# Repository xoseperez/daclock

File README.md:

# DA CLOCK

This repository contains the schematics and board layouts for Eagle of the different DaClock versions I've done so far.
The common parts between all these versions are: a microcontroller on board with some power management, an RTC and connectors for LED strips or matrices.

Current version is 3.0, based on ESP8266 and DS1337S, also features a buzzer and support for both WS2812 strips/matrices and 5050 "single color" strips.

## Versions

### Version 3.0 - WIFI LITE

This is the latest version of the DA CLOCK board, a custom ESP8266-based clock with an RTC, a buzzer and output to handle WS2812 strips.

#### Bill of materials for a WS2812-based clock

|Item|Buy|Quantity|CPU <sup>units</sup>|Total|
|---|---|---|---|---|
|Tinkerman Da Clock WIFI 3.0|[OSH Park](https://oshpark.com/shared_projects/gDLQyM9I)|1|6.57€ <sup>3</sup>|6.57€|
|Ai-Thinker ESP12F|[Aliexpress](http://s.click.aliexpress.com/e/mUZjemI) / [Ebay](https://rover.ebay.com/rover/1/711-53200-19255-0/1?icep_id=114&ipn=icep&toolid=20004&campid=5338044841&mpre=http%3A%2F%2Fwww.ebay.com%2Fitm%2FESP8266-Remote-Serial-Port-WIFI-Transceiver-Wireless-Module-Esp-12F-AP-STA-%2F272408386985%3Fhash%3Ditem3f6cce1da9%3Ag%3ArywAAOSwZJBX-7RV)|1|2.10€ <sup>5</sup>|2.10€|
|AMS1117-3.3|[Aliexpress](http://s.click.aliexpress.com/e/uj6iuNv) / [Ebay](https://rover.ebay.com/rover/1/711-53200-19255-0/1?icep_id=114&ipn=icep&toolid=20004&campid=5338044841&mpre=http%3A%2F%2Fwww.ebay.com%2Fitm%2FNew-10pcs-AMS1117-LM1117-3-3V-1A-SOT-223-Voltage-Regulator-NT00206-Ship-Today-%2F112049991237%3Fhash%3Ditem1a16b32e45%3Ag%3AqV8AAOSw14xWNwXc)|1|0.03€ <sup>50</sup>|0.03€|
|DS1337S|[Aliexpress](http://s.click.aliexpress.com/e/qbaAUr3) / [Ebay](https://rover.ebay.com/rover/1/711-53200-19255-0/1?icep_id=114&ipn=icep&toolid=20004&campid=5338044841&mpre=http%3A%2F%2Fwww.ebay.com%2Fitm%2F10-PCS-DS1337S-SOP-8-DS1337-1337-SMD-I2C-Serial-Real-Time-Clock-New-Original-%2F291774646835)|1|0.62€ <sup>10</sup>|0.62€|
|32KHz crystal|[Aliexpress](http://s.click.aliexpress.com/e/UVrrFmU) / [Ebay](https://rover.ebay.com/rover/1/711-53200-19255-0/1?icep_id=114&ipn=icep&toolid=20004&campid=5338044841&mpre=http%3A%2F%2Fwww.ebay.com%2Fitm%2FRALTRON-32-768KHz-Crystal-R38-32-768KHZ-R38-Style-Qty-10-%2F161261371100)|1|0.03€ <sup>50</sup>|0.03€|
|1N4148 SMD Diode|[Aliexpress](http://s.click.aliexpress.com/e/i2nayrB)|1|0.14€ <sup>10</sup>|0.14€|
|Buzzer|[Aliexpress](http://s.click.aliexpress.com/e/VbeAu3z) / [Ebay](https://rover.ebay.com/rover/1/711-53200-19255-0/1?icep_id=114&ipn=icep&toolid=20004&campid=5338044841&mpre=http%3A%2F%2Fwww.ebay.com%2Fitm%2FNew-10pcs-5v-Active-Buzzer-Continous-Beep-High-quality-The-sound-Alarm-HT00202-%2F281280117872)|1|0.15€<sup>10</sup>|0.15€|
|S8550 SMD NPN transistor|[Aliexpress](http://s.click.aliexpress.com/e/VZ3FYN7)|2|0.02€<sup>100</sup>|0.04€|
|100nF 0805 ceramic capacitor||1|0.01€ <sup>100</sup>|0.01€|
|1uF 10V 0805 tantalum capacitor|[Aliexpress](http://s.click.aliexpress.com/e/ey3ZVn2)|2|0.06€ <sup>50</sup>|0.12€|
|1000uF 16V electrolytic SMD capacitor|[Aliexpress](http://s.click.aliexpress.com/e/MjQ7eMf)|1|0.19€ <sup>10</sup>|0.19€|
|200Ohm 0805 resistor||1|0.01€ <sup>100</sup>|0.01€|
|10KOhm 0805 resistor||7|0.01€ <sup>100</sup>|0.07€|
|2 positions 5mm screw terminal|[Aliexpress](http://s.click.aliexpress.com/e/a2fqnM7)|1|0.06€ <sup>100</sup>|0.06€|
|3 positions 5mm screw terminal|[Aliexpress](http://s.click.aliexpress.com/e/Vjaa2RB)|1|0.07€ <sup>100</sup>|0.07€|
|3 position male header||1|0.01€ <sup>100</sup>|0.01€|
|5 position male header||1|0.01€ <sup>100</sup>|0.01€|
|Jumper||1|0.01€ <sup>100</sup>|0.01€|
|**Total**||||10.25€|

* (units) Minimum quantity for the stated price.
* Prices are based on the cheapest option, usually Aliexpress.
* Check the schematic (image or eagle file) for relation between parts and values.

### Version 2.1 - WIFI

### Version 1.2

## Firmware

* Project [Wordclock](https://bitbucket.org/xoseperez/wordclock) uses version 1.0 of this board (atmega328p based).
- Project [Slices](http://github.com/xoseperez/slices) uses version 3.0 of this board (ESP8266 based).

## Open Hardware

Hardware designs (schematics and CAD) files are licensed under the [Creative Commons Attribution-ShareAlike 3.0 Unported License](http://creativecommons.org/licenses/by-sa/3.0/) and follow the terms of the [OSHW (Open-source hardware) Statement of Principles 1.0.](http://freedomdefined.org/OSHW)

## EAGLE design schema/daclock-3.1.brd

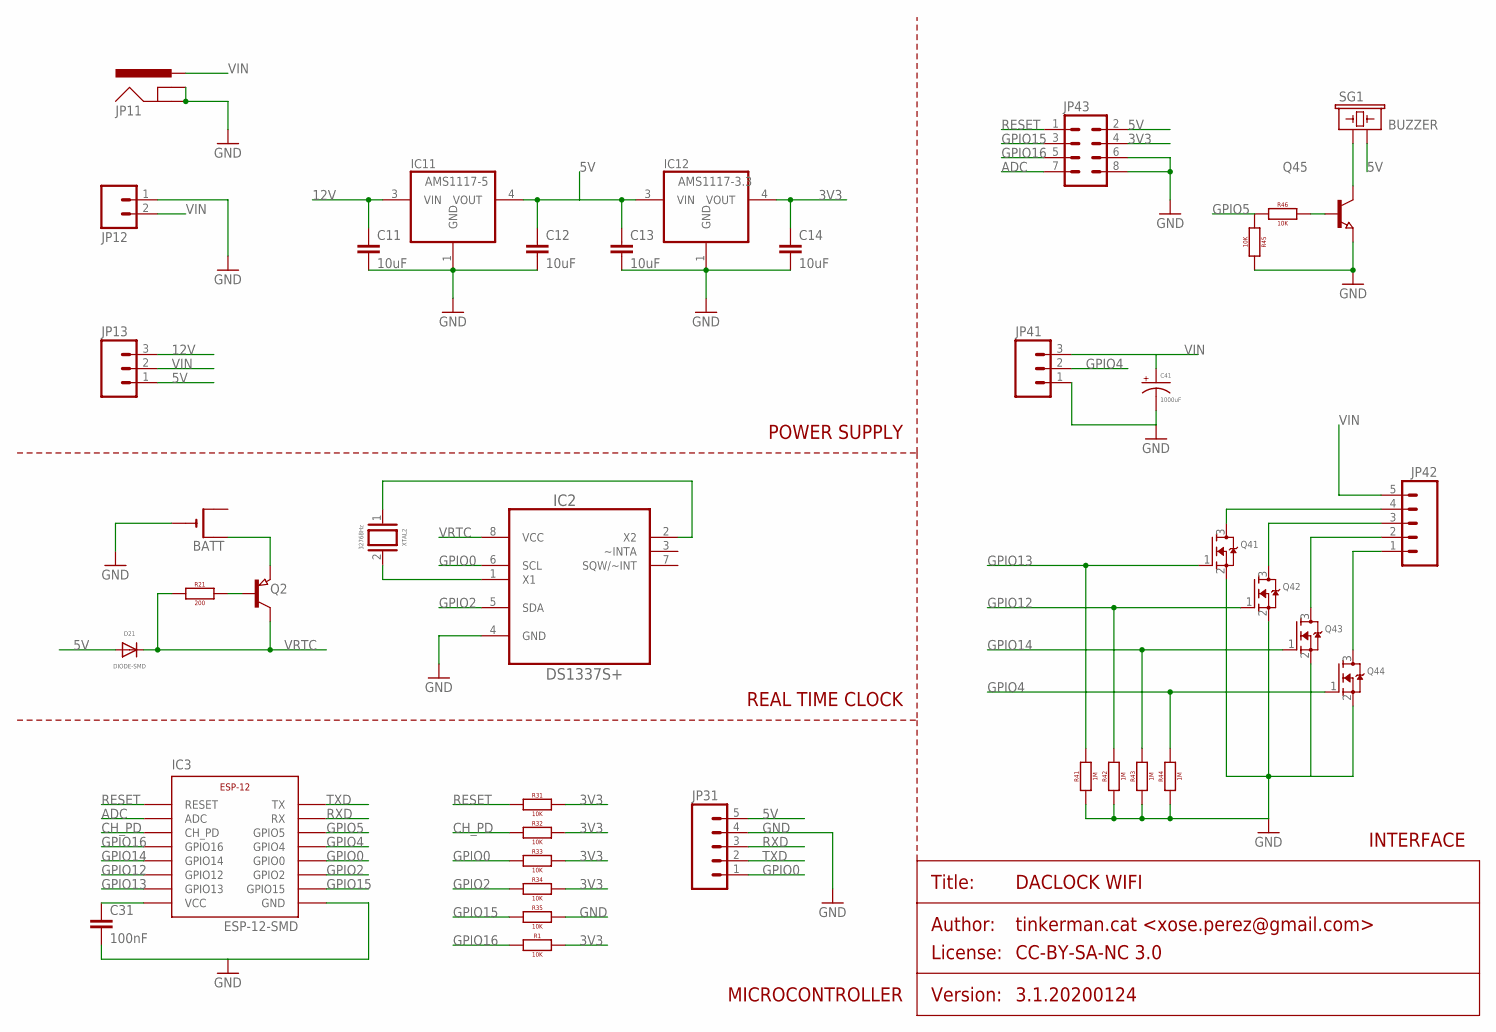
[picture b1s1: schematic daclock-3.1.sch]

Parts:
BATT: CR2032SMT; CR2032-SMD
C11, C12, C13, C14: 10uF; 0805
C31: 100nF; 0805
C41: 1000uF; PANASONIC_G
D21: DIODE-SMD; 0805_DIODE
IC2: DS1337S+; SOIC127P600X175-8N
IC3: ESP-12-SMD
IC11: AMS1117-5; SOT223
IC12: AMS1117-3.3; SOT223
JP11: POWER_JACKPTH; POWER_JACK_PTH
JP12: M02200MIL; SCREWTERMINAL-200MIL-2
JP13: M03PTH; 1X03
JP31, JP42: M05NO_SILK; 1X05_NO_SILK
JP41: M03200MIL; SCREWTERMINAL-200MIL-3
JP43: M04X2; 2X4
Q2: PNP-TRANSISTOR_SOT23; SOT23
Q41, Q42, Q43, Q44: MOSFET-NREFLOW; SOT23
Q45: NPN-TRANSISTOR_SOT23; SOT23
R1, R31, R32, R33, R34, R35, R45, R46: 10K; 0805
R21: 200; 0805
R41, R42, R43, R44: 1M; 0805
SG1: BUZZER; BUZZER-12MM
XTAL2: 32768Hz; TC38H

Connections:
3V3: C14.1, C31.1, IC3.VCC, IC12.4 (VOUT), JP43.4, R1.2, R31.2, R32.2, R33.2, R34.2
5V: C12.1, C13.1, D21.A, IC11.4 (VOUT), IC12.3 (VIN), JP13.1, JP31.5, JP43.2, SG1.- (2)
12V: C11.1, IC11.3 (VIN), JP13.3
ADC: IC3.ADC, JP43.7
CH_PD: IC3.CH_PD, R32.1
GND: BATT.-, C11.2, C12.2, C13.2, C14.2, C31.2, C41.-, IC2.4 (GND), IC3.GND, IC11.1 (GND), IC12.1 (GND), JP11.GND, JP11.GNDBREAK, JP12.1, JP31.4, JP41.1, JP43.6, JP43.8, Q41.2 (S), Q42.2 (S), Q43.2 (S), Q44.2 (S), Q45.2 (E), R35.2, R41.1, R42.1, R43.1, R44.1, R45.2
GPIO0: IC2.6 (SCL), IC3.GPIO0, JP31.1, R33.1
GPIO2: IC2.5 (SDA), IC3.GPIO2, R34.1
GPIO4: IC3.GPIO4, JP41.2, Q44.1 (G), R44.2
GPIO5: IC3.GPIO5, R45.1, R46.1
GPIO12: IC3.GPIO12, Q42.1 (G), R42.2
GPIO13: IC3.GPIO13, Q41.1 (G), R41.2
GPIO14: IC3.GPIO14, Q43.1 (G), R43.2
GPIO15: IC3.GPIO15, JP43.3, R35.1
GPIO16: IC3.GPIO16, JP43.5, R1.1
unnamed: Q45.1 (B), R46.2
unnamed: IC2.1 (X1), XTAL2.2
unnamed: IC2.2 (X2), XTAL2.1
unnamed: JP42.4, Q41.3 (D)
unnamed: Q2.1 (B), R21.2
unnamed: JP42.3, Q42.3 (D)
unnamed: BATT.+$1 (+), Q2.2 (E)
unnamed: JP42.2, Q43.3 (D)
unnamed: JP42.1, Q44.3 (D)
unnamed: Q45.3 (C), SG1.+ (1)
RESET: IC3.RESET, JP43.1, R31.1
RXD: IC3.RX, JP31.3
TXD: IC3.TX, JP31.2
VIN: C41.+, JP11.PWR, JP12.2, JP13.2, JP41.3, JP42.5
VRTC: D21.C, IC2.8 (VCC), Q2.3 (C), R21.1

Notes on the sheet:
POWER SUPPLY
REAL TIME CLOCK
MICROCONTROLLER
INTERFACE

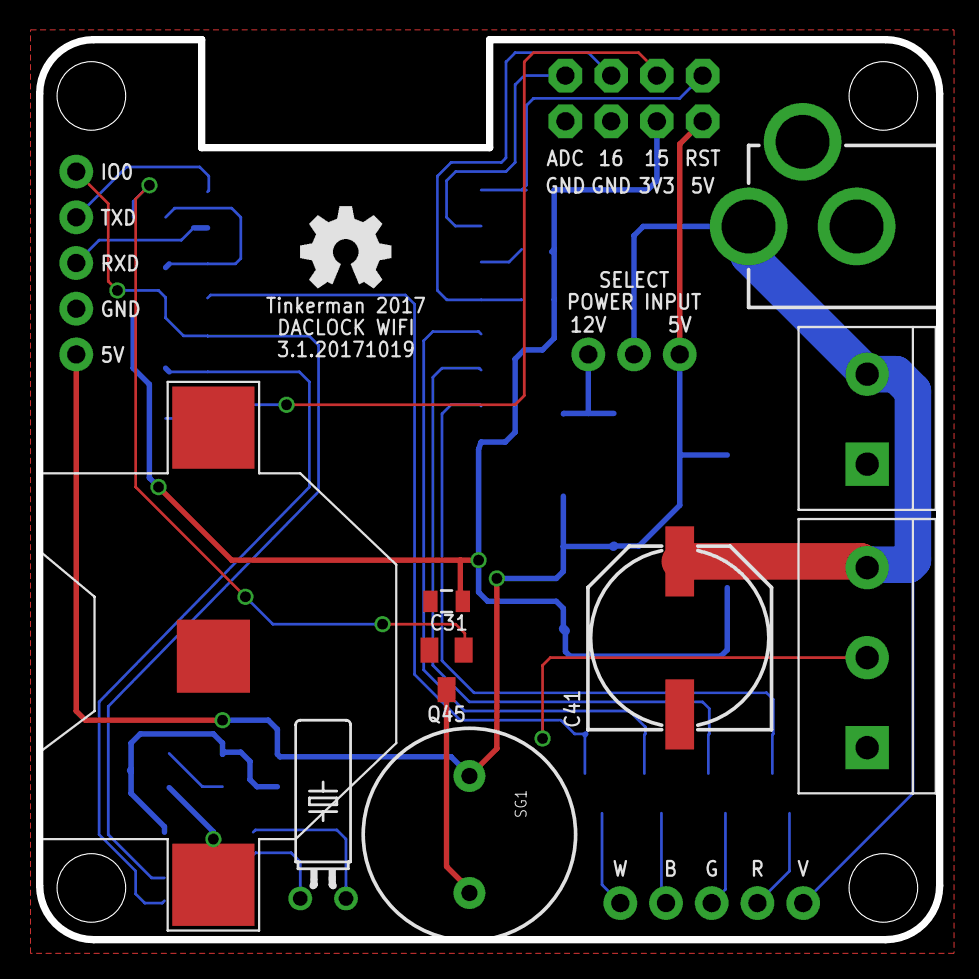
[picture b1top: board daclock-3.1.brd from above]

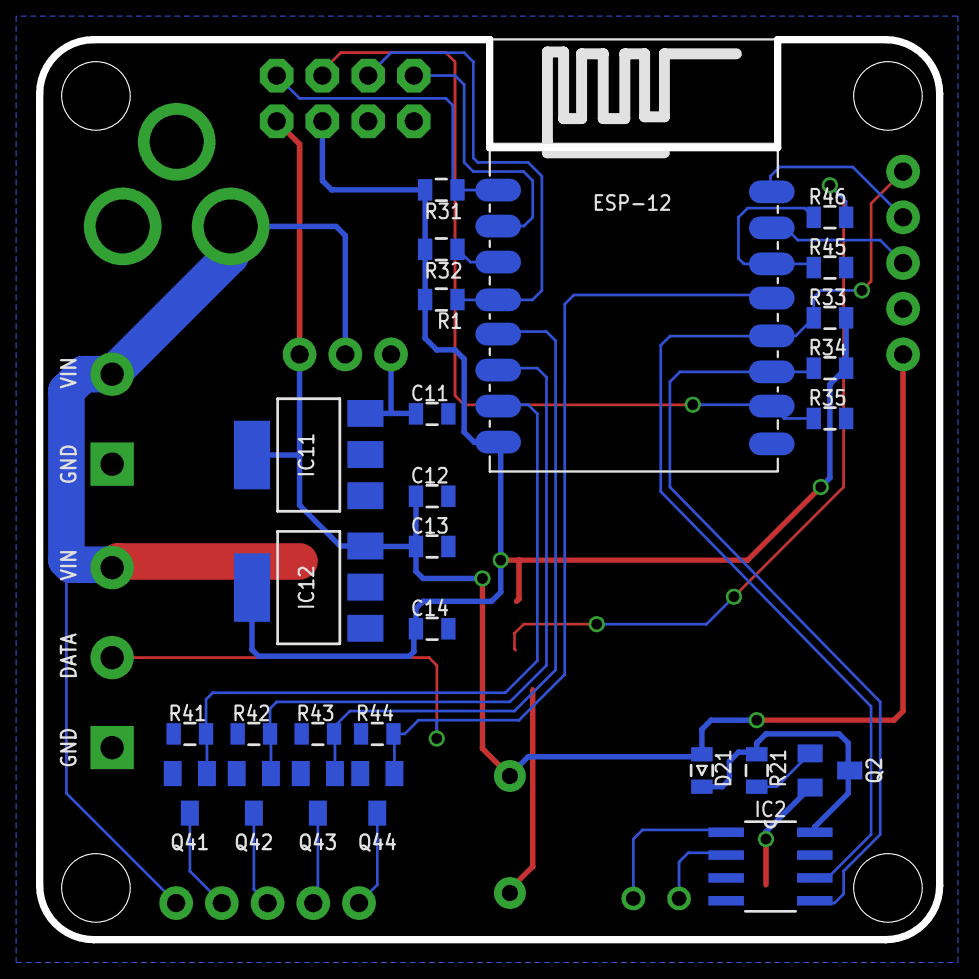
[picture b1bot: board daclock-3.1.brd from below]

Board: 2 copper layers, 50.0 x 50.0 mm, 40 parts (27 on the bottom side), 30 nets.

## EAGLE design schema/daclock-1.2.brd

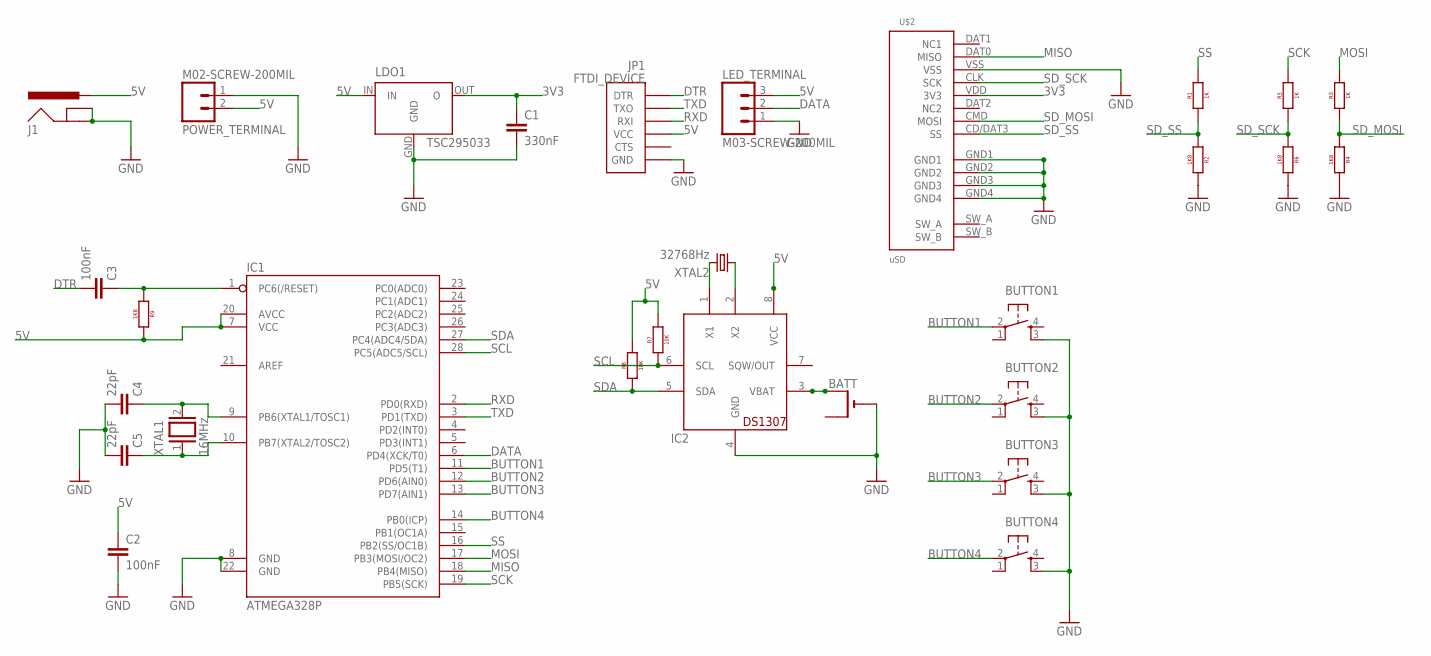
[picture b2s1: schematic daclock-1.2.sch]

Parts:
BATT: CR2032SMT; CR2032-SMD
BUTTON1: B1; TACTILE_BUTTON
BUTTON2: B2; TACTILE_BUTTON
BUTTON3: B3; TACTILE_BUTTON
BUTTON4: B4; TACTILE_BUTTON
C1: 330nF; C050-025X075
C2, C3: 100nF; C050-025X075
C4, C5: 22pF; C050-025X075
IC1: ATMEGA328P; DIL28-3
IC2: DS1307; DIL08
J1: POWER_JACKPTH; POWER_JACK_PTH
JP1: FTDI_DEVICE; FTDI_DEVICE_SIDE
LDO1: TSC295033; TO92
LED_TERMINAL: M03-SCREW-200MIL; SCREWTERMINAL-200MIL-3
POWER_TERMINAL: M02-SCREW-200MIL; SCREWTERMINAL-200MIL-2
R1, R3, R5: 1K; AXIAL-0.4
R2, R4, R6, R9: 1K8; AXIAL-0.4
R7, R8: 10K; AXIAL-0.4
U$2: uSD; DM3D
XTAL1: 16MHz; QS
XTAL2: 32768Hz; TC38H

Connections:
3V3: C1.1, LDO1.OUT (O), U$2.VDD (3V3)
5V: C2.1, IC1.7 (VCC), IC1.20 (AVCC), IC2.8 (VCC), J1.PWR, JP1.P$4 (VCC), LDO1.IN, LED_TERMINAL.3, POWER_TERMINAL.2, R7.P$2 (2), R8.P$2 (2), R9.P$2 (2)
BUTTON1: BUTTON1.2 (SWA1), IC1.11 (PD5(T1))
BUTTON2: BUTTON2.2 (SWA1), IC1.12 (PD6(AIN0))
BUTTON3: BUTTON3.2 (SWA1), IC1.13 (PD7(AIN1))
BUTTON4: BUTTON4.2 (SWA1), IC1.14 (PB0(ICP))
DATA: IC1.6 (PD4(XCK/T0)), LED_TERMINAL.2
DTR: C3.2, JP1.P$1 (DTR)
GND: BATT.-, BUTTON1.3 (SWB2), BUTTON2.3 (SWB2), BUTTON3.3 (SWB2), BUTTON4.3 (SWB2), C1.2, C2.2, C4.2, C5.2, IC1.8 (GND), IC1.22 (GND), IC2.4 (GND), J1.GND, J1.GNDBREAK, JP1.P$6 (GND), LDO1.GND, LED_TERMINAL.1, POWER_TERMINAL.1, R2.P$2 (2), R4.P$2 (2), R6.P$2 (2), U$2.GND1, U$2.GND2, U$2.GND3, U$2.GND4, U$2.VSS
MISO: IC1.18 (PB4(MISO)), U$2.DAT0 (MISO)
MOSI: IC1.17 (PB3(MOSI/OC2)), R3.P$2 (2)
unnamed: C3.1, IC1.1 (PC6(/RESET)), R9.P$1 (1)
unnamed: C4.1, IC1.9 (PB6(XTAL1/TOSC1)), XTAL1.2
unnamed: C5.1, IC1.10 (PB7(XTAL2/TOSC2)), XTAL1.1
unnamed: BATT.+$1 (+), IC2.3 (VBAT)
unnamed: IC2.1 (X1), XTAL2.2
unnamed: IC2.2 (X2), XTAL2.1
RXD: IC1.2 (PD0(RXD)), JP1.P$3 (RXI)
SCK: IC1.19 (PB5(SCK)), R5.P$2 (2)
SCL: IC1.28 (PC5(ADC5/SCL)), IC2.6 (SCL), R7.P$1 (1)
SDA: IC1.27 (PC4(ADC4/SDA)), IC2.5 (SDA), R8.P$1 (1)
SD_MOSI: R3.P$1 (1), R4.P$1 (1), U$2.CMD (MOSI)
SD_SCK: R5.P$1 (1), R6.P$1 (1), U$2.CLK (SCK)
SD_SS: R1.P$1 (1), R2.P$1 (1), U$2.CD/DAT3 (SS)
SS: IC1.16 (PB2(SS/OC1B)), R1.P$2 (2)
TXD: IC1.3 (PD1(TXD)), JP1.P$2 (TXO)

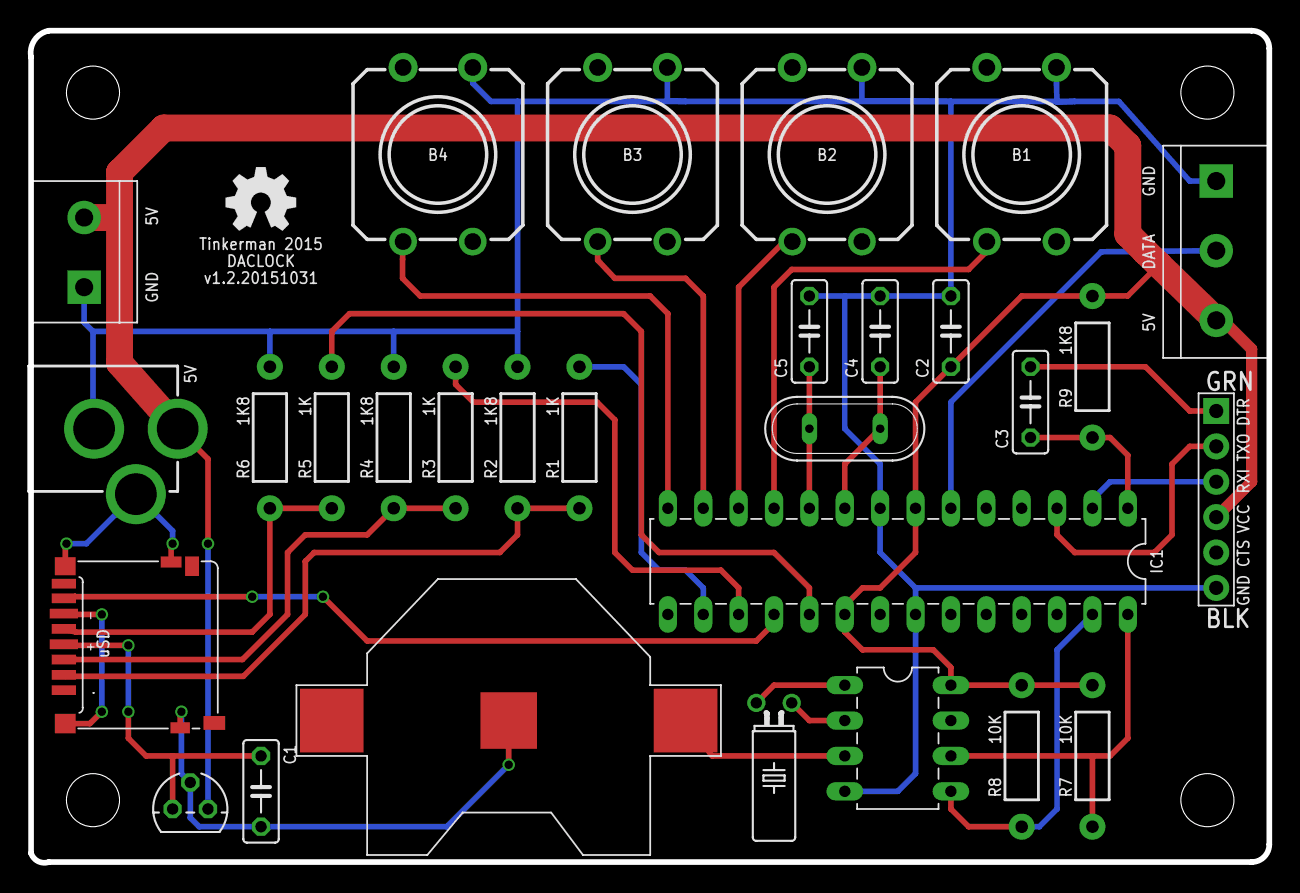
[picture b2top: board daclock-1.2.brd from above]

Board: 2 copper layers, 88.9 x 59.7 mm, 29 parts (0 on the bottom side), 26 nets.

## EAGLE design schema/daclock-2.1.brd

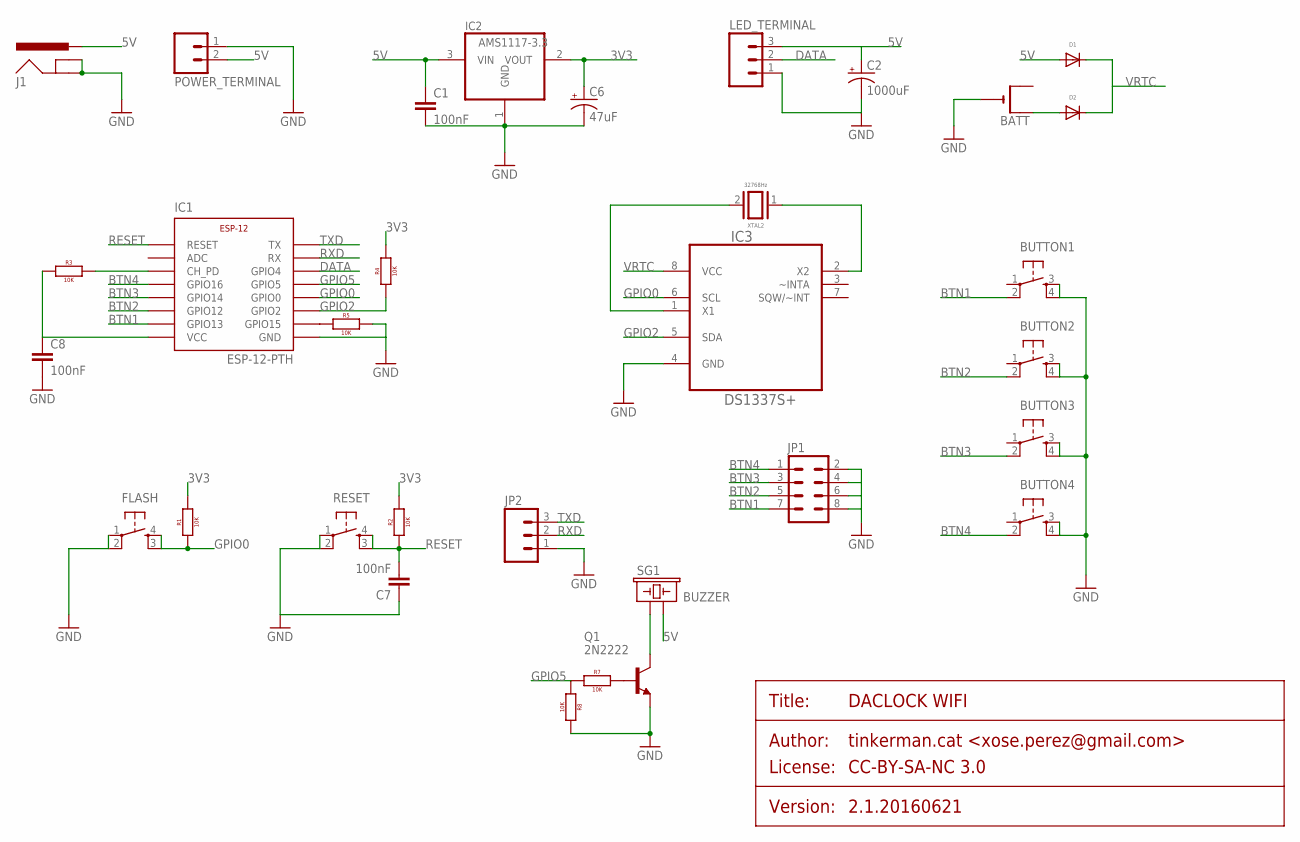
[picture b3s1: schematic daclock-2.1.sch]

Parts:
BATT: CR2032SMT; CR2032-SMD
BUTTON1: BTN1; TACTILE-BUTTON
BUTTON2: BTN2; TACTILE-BUTTON
BUTTON3: BTN3; TACTILE-BUTTON
BUTTON4: BTN4; TACTILE-BUTTON
C1, C7, C8: 100nF; C050-025X075
C2: 1000uF; PANASONIC_G
C6: 47uF; CPOL-RADIAL-10UF-25V
D1, D2: DIODE-PTH4; AXIAL-0.4-DIODE
FLASH: TACTILE_BUTTON_SMD; TACTILE-BUTTON-SMD
IC1: ESP-12-PTH
IC2: AMS1117-3.3; SOT223
IC3: DS1337S+; SOIC127P600X175-8N
J1: POWER_JACKPTH; POWER_JACK_PTH
JP1: M04X2; 2X4
JP2: M03PTH; 1X03
LED_TERMINAL: M03200MIL; SCREWTERMINAL-200MIL-3
POWER_TERMINAL: M02200MIL; SCREWTERMINAL-200MIL-2
Q1: 2N2222; TO92-EBC-OVAL
R1, R2, R3, R4, R5, R7, R8: 10K; AXIAL-0.4
RESET: TACTILE_BUTTON_SMD; TACTILE-BUTTON-SMD
SG1: BUZZER; BUZZER-12MM
XTAL2: 32768Hz; TC38H

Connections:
3V3: C6.1 (+), C8.1, IC1.VCC, IC2.2 (VOUT), R1.P$2 (2), R2.P$2 (2), R3.P$1 (1), R4.P$2 (2)
5V: C1.1, C2.+, D1.A, IC2.3 (VIN), J1.PWR, LED_TERMINAL.3, POWER_TERMINAL.2, SG1.- (2)
BTN1: BUTTON1.2 (SWB1), IC1.GPIO13, JP1.7
BTN2: BUTTON2.2 (SWB1), IC1.GPIO12, JP1.5
BTN3: BUTTON3.2 (SWB1), IC1.GPIO14, JP1.3
BTN4: BUTTON4.2 (SWB1), IC1.GPIO16, JP1.1
DATA: IC1.GPIO4, LED_TERMINAL.2
GND: BATT.-, BUTTON1.3 (SWA2), BUTTON1.4 (SWB2), BUTTON2.3 (SWA2), BUTTON2.4 (SWB2), BUTTON3.3 (SWA2), BUTTON3.4 (SWB2), BUTTON4.3 (SWA2), BUTTON4.4 (SWB2), C1.2, C2.-, C6.2 (-), C7.1, C8.2, FLASH.1 (SWA1), FLASH.2 (SWB1), IC1.GND, IC2.1 (GND), IC3.4 (GND), J1.GND, J1.GNDBREAK, JP1.2, JP1.4, JP1.6, JP1.8, JP2.1, LED_TERMINAL.1, POWER_TERMINAL.1, Q1.E, R5.P$2 (2), R8.P$2 (2), RESET.1 (SWA1), RESET.2 (SWB1)
GPIO0: FLASH.3 (SWB2), FLASH.4 (SWA2), IC1.GPIO0, IC3.6 (SCL), R1.P$1 (1)
GPIO2: IC1.GPIO2, IC3.5 (SDA), R4.P$1 (1)
GPIO5: IC1.GPIO5, R7.P$1 (1), R8.P$1 (1)
unnamed: Q1.B, R7.P$2 (2)
unnamed: IC3.1 (X1), XTAL2.2
unnamed: IC3.2 (X2), XTAL2.1
unnamed: BATT.+$1 (+), D2.A
unnamed: IC1.CH_PD, R3.P$2 (2)
unnamed: IC1.GPIO15, R5.P$1 (1)
unnamed: Q1.C, SG1.+ (1)
RESET: C7.2, IC1.RESET, R2.P$1 (1), RESET.3 (SWB2), RESET.4 (SWA2)
RXD: IC1.RX, JP2.2
TXD: IC1.TX, JP2.3
VRTC: D1.C, D2.C, IC3.8 (VCC)

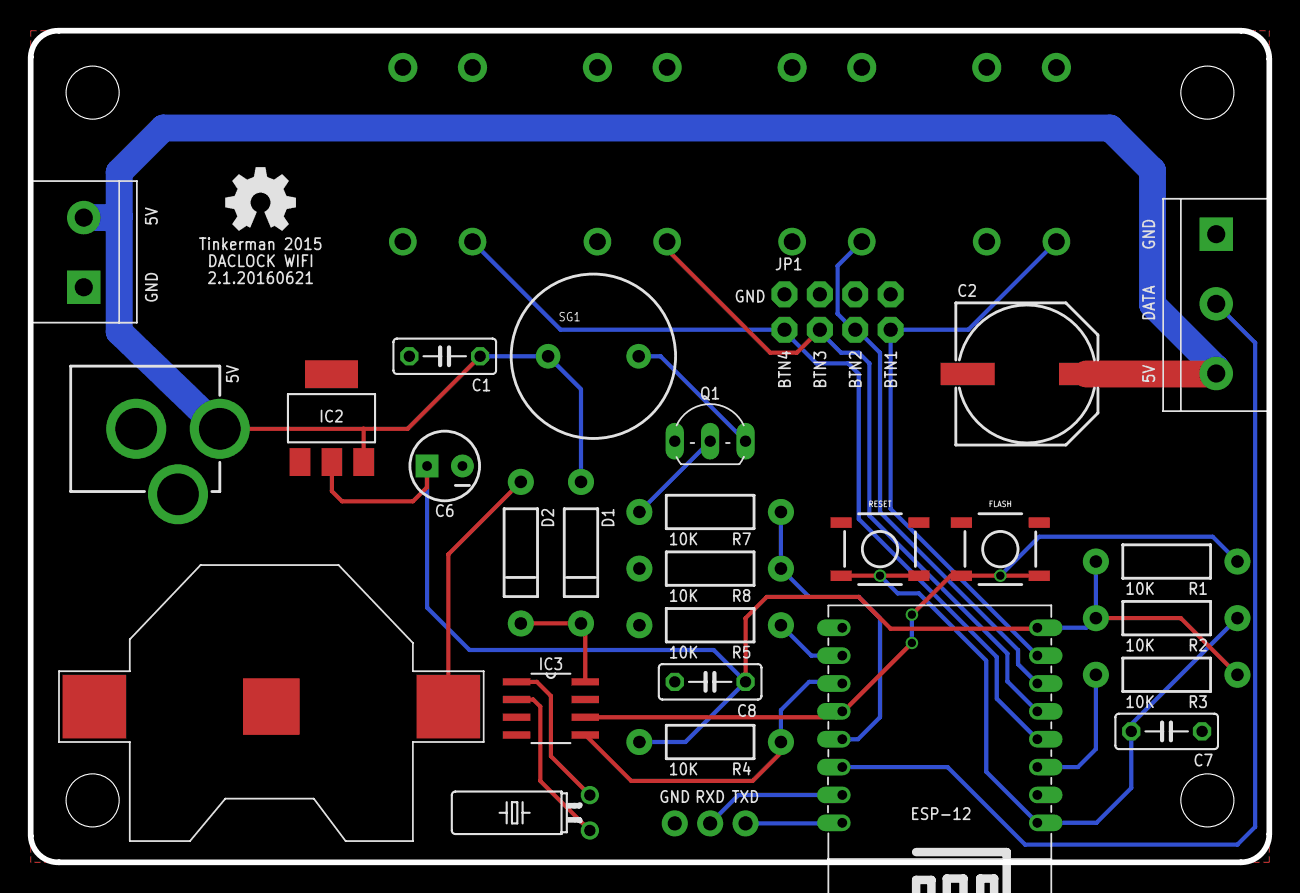
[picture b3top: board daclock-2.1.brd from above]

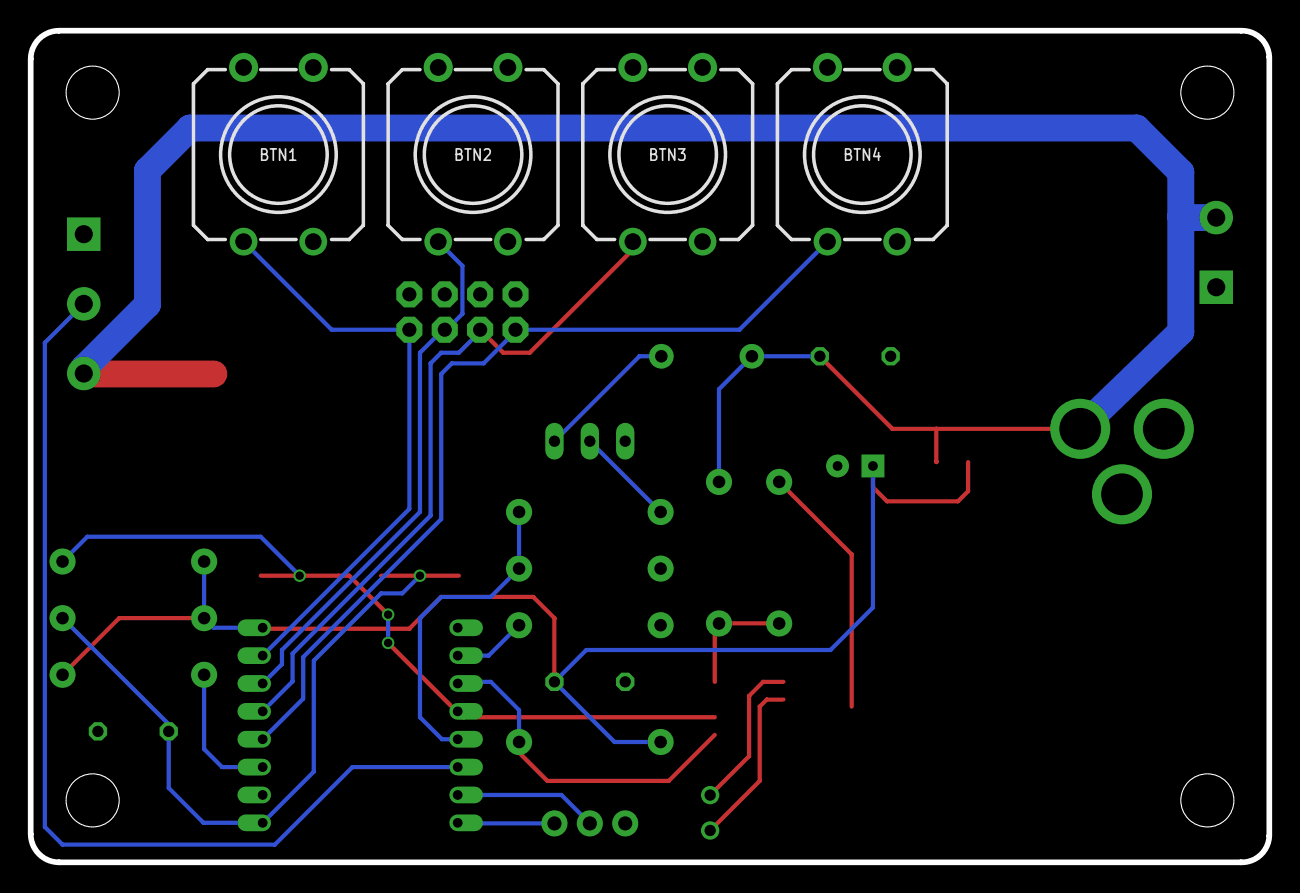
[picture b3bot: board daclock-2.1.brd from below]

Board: 2 copper layers, 88.9 x 59.7 mm, 32 parts (4 on the bottom side), 22 nets.

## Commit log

2017-05-01 Added image, reverse versions and fix BOM layout

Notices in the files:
schema/daclock-2.1.sch:
PROJECT_LICENSE: CC-BY-SA-NC 3.0
parts and their libraries:
SparkFun-Connectors: Licensing: CC v3.0 Share-Alike You are welcome to use this library for commercial purposes.
SparkFun-Aesthetics: Licensing: Creative Commons ShareAlike 4.0 International - https://creativecommons.org/licenses/by-sa/4.0
